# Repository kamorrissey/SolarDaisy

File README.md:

# SolarDaisy

## Introduction
The SolarDaisy is an open-source solar garden light with animated LEDs.
The LEDs animate only in relative darkness.
All files needed to reproduce the device are included.

A 2V solar panel charges an AA 1.2V NiMH cell through a 1N5817 Schottky diode to limit current backflow from the cell to the panel.
The cell (possibly in addition to the panel) is boosted to 3.3V with a TPS613222 boost-buck regulator.
The regulator powers a PIC16F13115 microcontroller (MCU), which drives the LEDs of the light.

There are two groups of LEDs:
* a center color-cycling standard LED is on only when the MCU detects darkness
* a ring of six white, high-brightness, 3V standard LEDs
  are animated using three-wire [Charlieplexing](https://en.wikipedia.org/wiki/Charlieplexing),
  time-division multiplexing, and PWM (for brightness control)

There is a circular main PCB.
A breakaway portion is used in the charging section of the device.

The post and charging section, with a solar panel and battery holder, from a commercial solar garden walkway light are used to simplify manufacturing.
The 3d-printed parts are of modular design so that only one part need be redesigned to use a different walkway light.

## Project Layout
There are four primary folders:
  1. [artifacts](artifacts) - files from the original project deemed worth archiving
  1. [kicad](kicad) - KiCad projects for PCB designs
  1. [mplab](mplab) - MPLAB X projects for the firmware
  1. [solidworks](solidworks) - SOLIDWORKS CAD projects for 3d printable parts

## Building
Can be built with [MPLAB X IDE](https://www.microchip.com/mplab-x-ide)
or [MPLAB for VS Code](https://www.microchip.com/en-us/tools-resources/develop/mplab-tools-vs-code)
by opening the folder mplab/solar-charlie-16f13115.X in the desired MPLAB tool.

(Remainder to be provided)

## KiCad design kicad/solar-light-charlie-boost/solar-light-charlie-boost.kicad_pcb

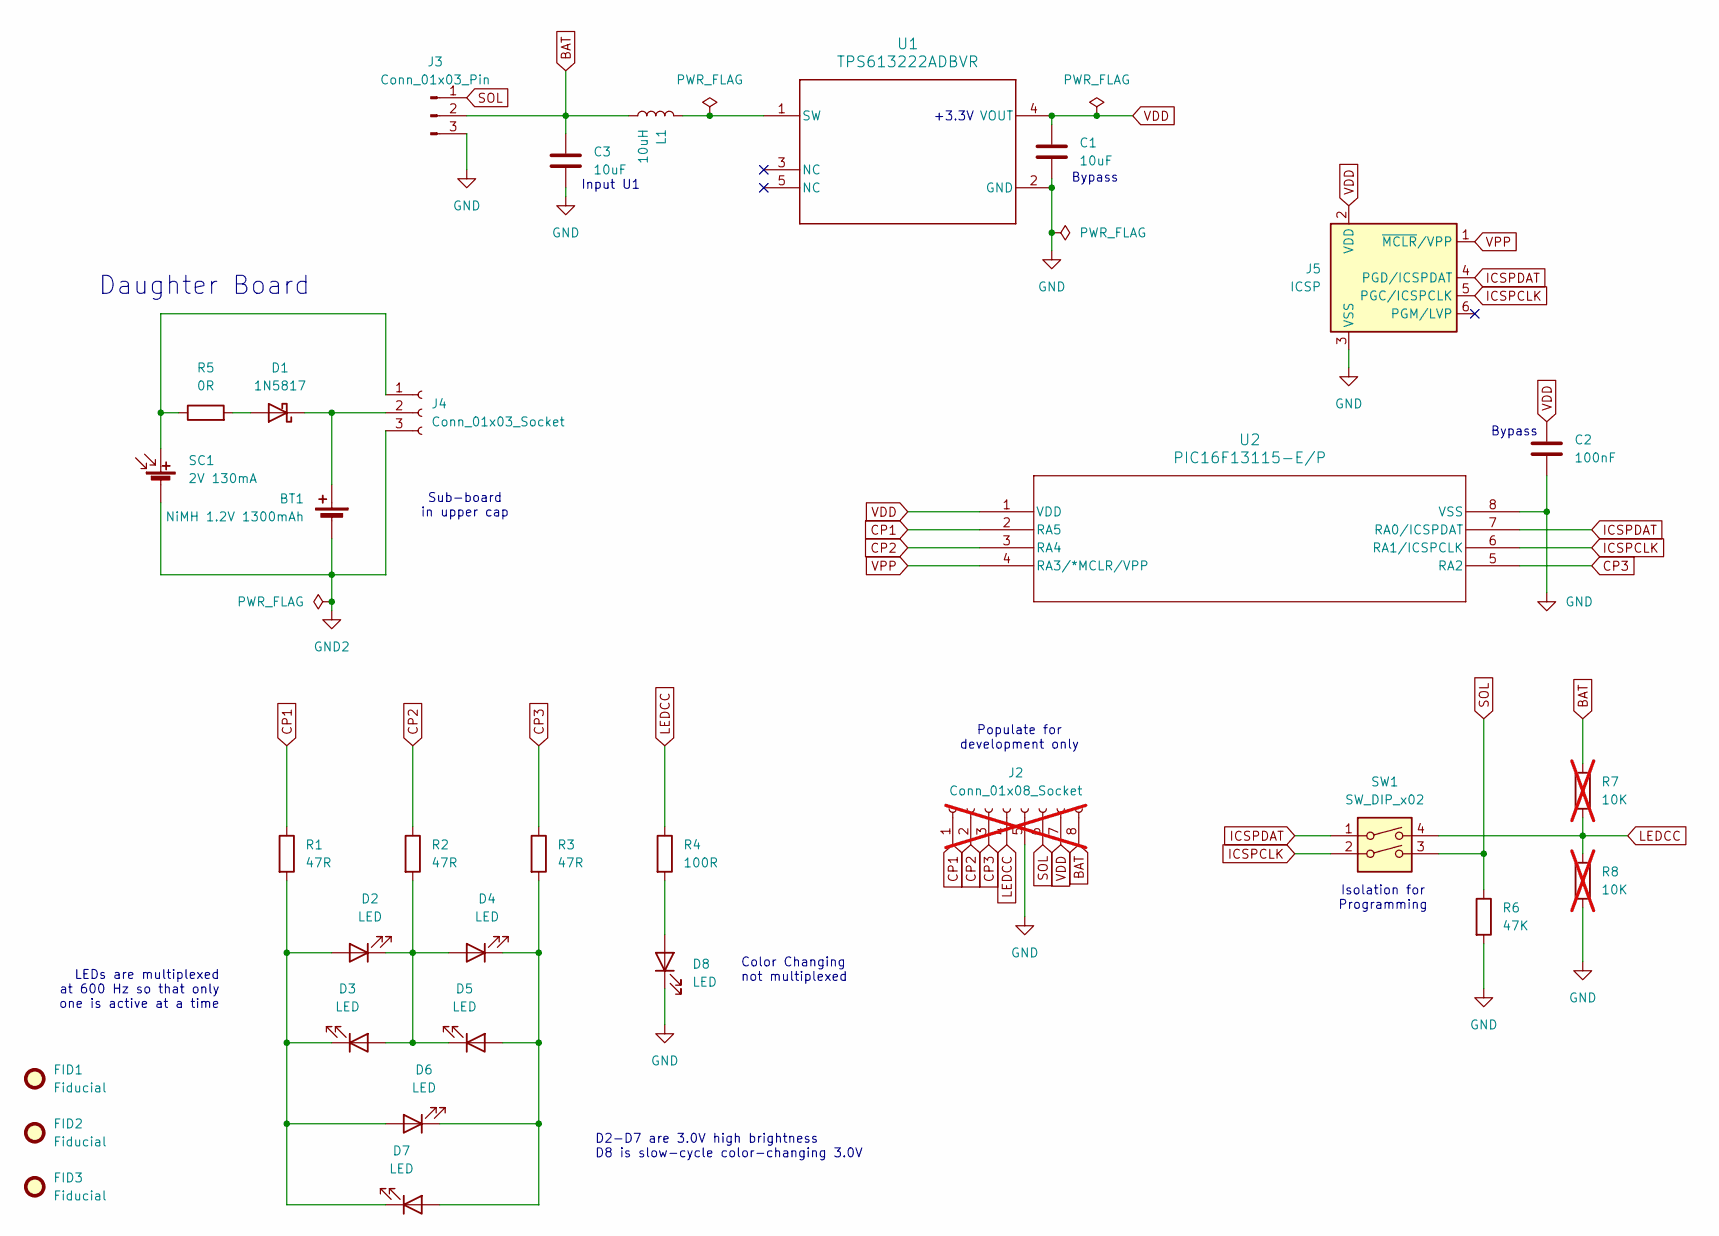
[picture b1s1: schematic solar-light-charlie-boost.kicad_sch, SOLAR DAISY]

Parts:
BT1: NiMH 1.2V 1300mAh; SolderWire-0.1sqmm_1x02_P3.6mm_D0.4mm_OD1mm
C1, C3: 10uF; C_Disc_D3.0mm_W2.0mm_P2.50mm
C2: 100nF; C_Disc_D3.0mm_W2.0mm_P2.50mm
D1: 1N5817; D_DO-41_SOD81_P10.16mm_Horizontal
D2, D3, D4, D5, D6, D7, D8: LED; LED_D5.0mm
FID1, FID2, FID3: Fiducial; Fiducial_0.5mm_Mask1mm
J2: Conn_01x08_Socket; PinSocket_1x08_P2.54mm_Vertical; not fitted
J3: Conn_01x03_Pin; JST_PH_B3B-PH-K_1x03_P2.00mm_Vertical
J4: Conn_01x03_Socket; SolderWire-0.1sqmm_1x03_P3.6mm_D0.4mm_OD1mm
J5: ICSP; PinHeader_1x06_P2.54mm_Horizontal
L1: 10uH; L_Axial_L5.0mm_D3.6mm_P10.00mm_Horizontal_Murata_BL01RN1A2A2
R1, R2, R3: 47R; R_Axial_DIN0207_L6.3mm_D2.5mm_P10.16mm_Horizontal
R4: 100R; R_Axial_DIN0207_L6.3mm_D2.5mm_P10.16mm_Horizontal
R5: 0R; R_Axial_DIN0207_L6.3mm_D2.5mm_P10.16mm_Horizontal
R6: 47K; R_Axial_DIN0207_L6.3mm_D2.5mm_P10.16mm_Horizontal
R7, R8: 10K; R_Axial_DIN0207_L6.3mm_D2.5mm_P10.16mm_Horizontal; not fitted
SC1: 2V 130mA; SolderWire-0.1sqmm_1x02_P3.6mm_D0.4mm_OD1mm
SW1: SW_DIP_x02; SW_DIP_SPSTx02_Slide_6.7x6.64mm_W7.62mm_P2.54mm_LowProfile
U1: TPS613222ADBVR; SOT-23-5_HandSoldering
U2: PIC16F13115-E/P; DIP-8_W7.62mm

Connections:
BAT: C3.1, J2.8, J3.2, L1.1, R7.1
CP1: J2.1, R1.1, U2.2 (RA5)
CP2: J2.2, R2.1, U2.3 (RA4)
CP3: J2.3, R3.1, U2.5 (RA2)
GND: C1.2, C2.1, C3.2, D8.1 (K), J2.5, J3.3, J5.3 (VSS), R6.2, R8.2, U1.2 (GND), U2.8 (VSS)
GND2: BT1.2 (-), J4.3, SC1.2 (-)
ICSPCLK: J5.5 (PGC/ICSPCLK), SW1.2, U2.6 (RA1/ICSPCLK)
ICSPDAT: J5.4 (PGD/ICSPDAT), SW1.1, U2.7 (RA0/ICSPDAT)
LEDCC: J2.4, R4.1, R7.2, R8.1, SW1.4
unnamed: BT1.1 (+), D1.1 (K), J4.2
unnamed: D1.2 (A), R5.2
unnamed: D2.2 (A), D3.1 (K), D6.2 (A), D7.1 (K), R1.2
unnamed: D2.1 (K), D3.2 (A), D4.2 (A), D5.1 (K), R2.2
unnamed: D4.1 (K), D5.2 (A), D6.1 (K), D7.2 (A), R3.2
unnamed: D8.2 (A), R4.2
unnamed: J4.1, R5.1, SC1.1 (+)
unnamed: L1.2, U1.1 (SW)
SOL: J2.6, J3.1, R6.1, SW1.3
VDD: C1.1, C2.2, J2.7, J5.2 (VDD), U1.4 (VOUT), U2.1 (VDD)
VPP: J5.1 (~MCLR/VPP), U2.4 (RA3/*MCLR/VPP)

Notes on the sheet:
Isolation for Programming
LEDs are multiplexed at 600 Hz so that only one is active at a time
+3.3V
Input U1
Daughter Board
Sub-board in upper cap
Bypass
D2-D7 are 3.0V high brightness D8 is slow-cycle color-changing 3.0V
Color Changing not multiplexed
Populate for development only

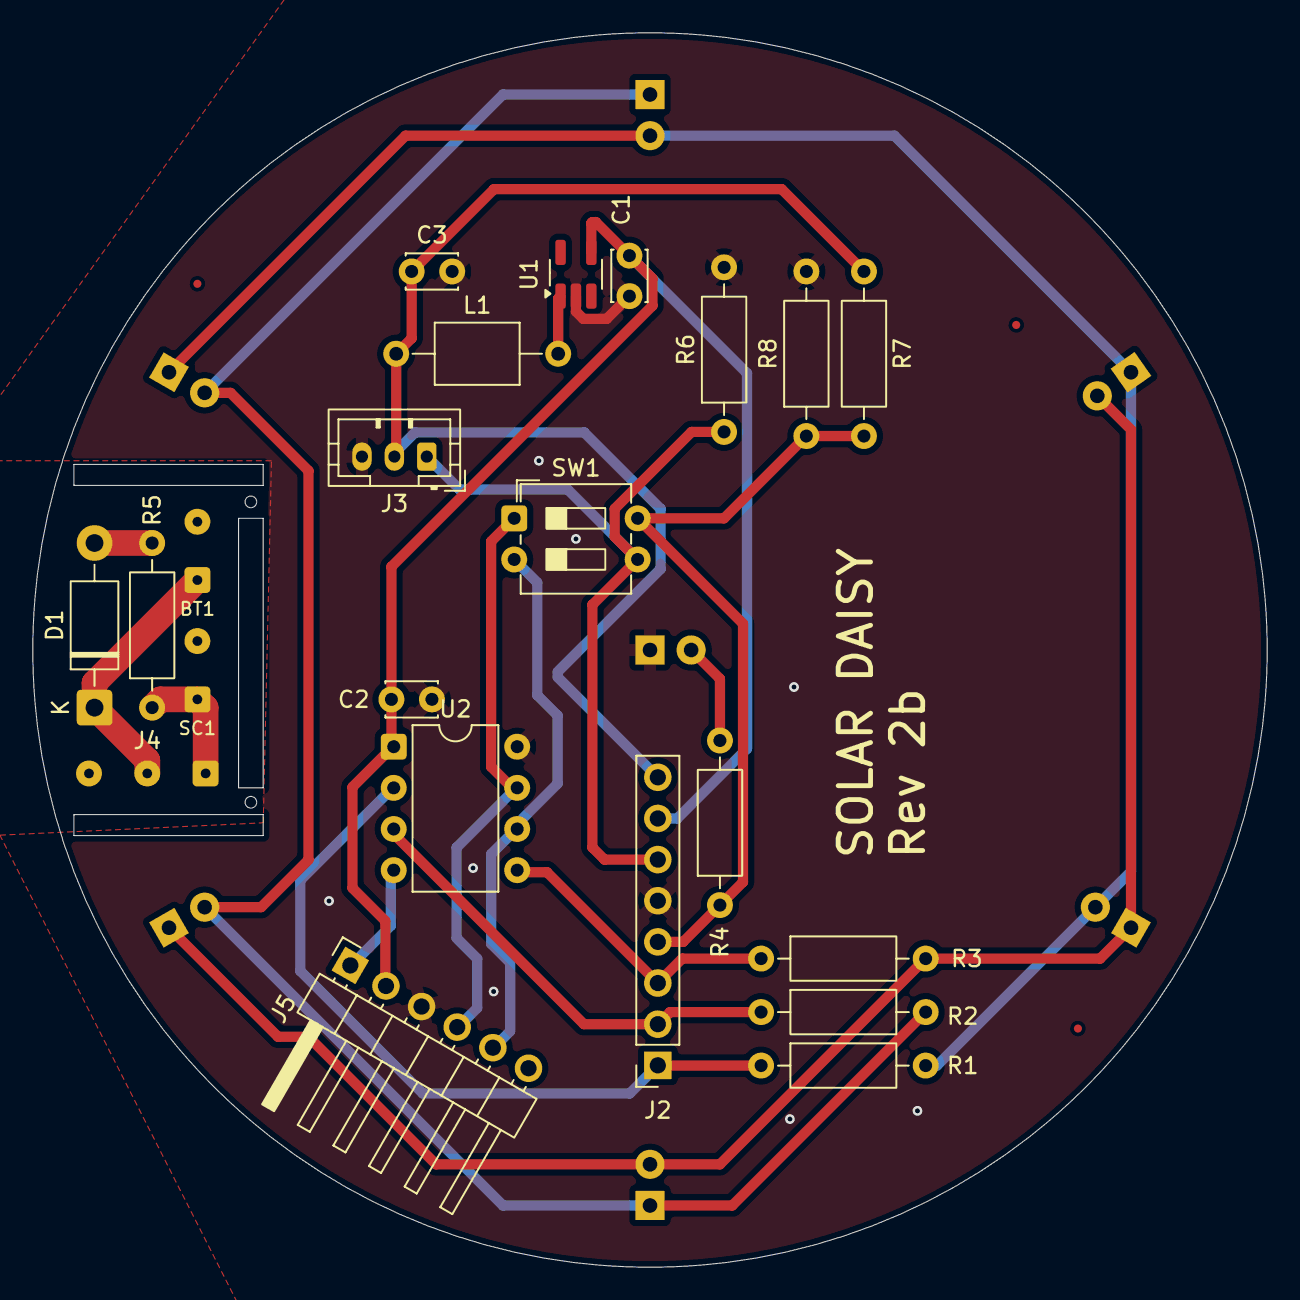
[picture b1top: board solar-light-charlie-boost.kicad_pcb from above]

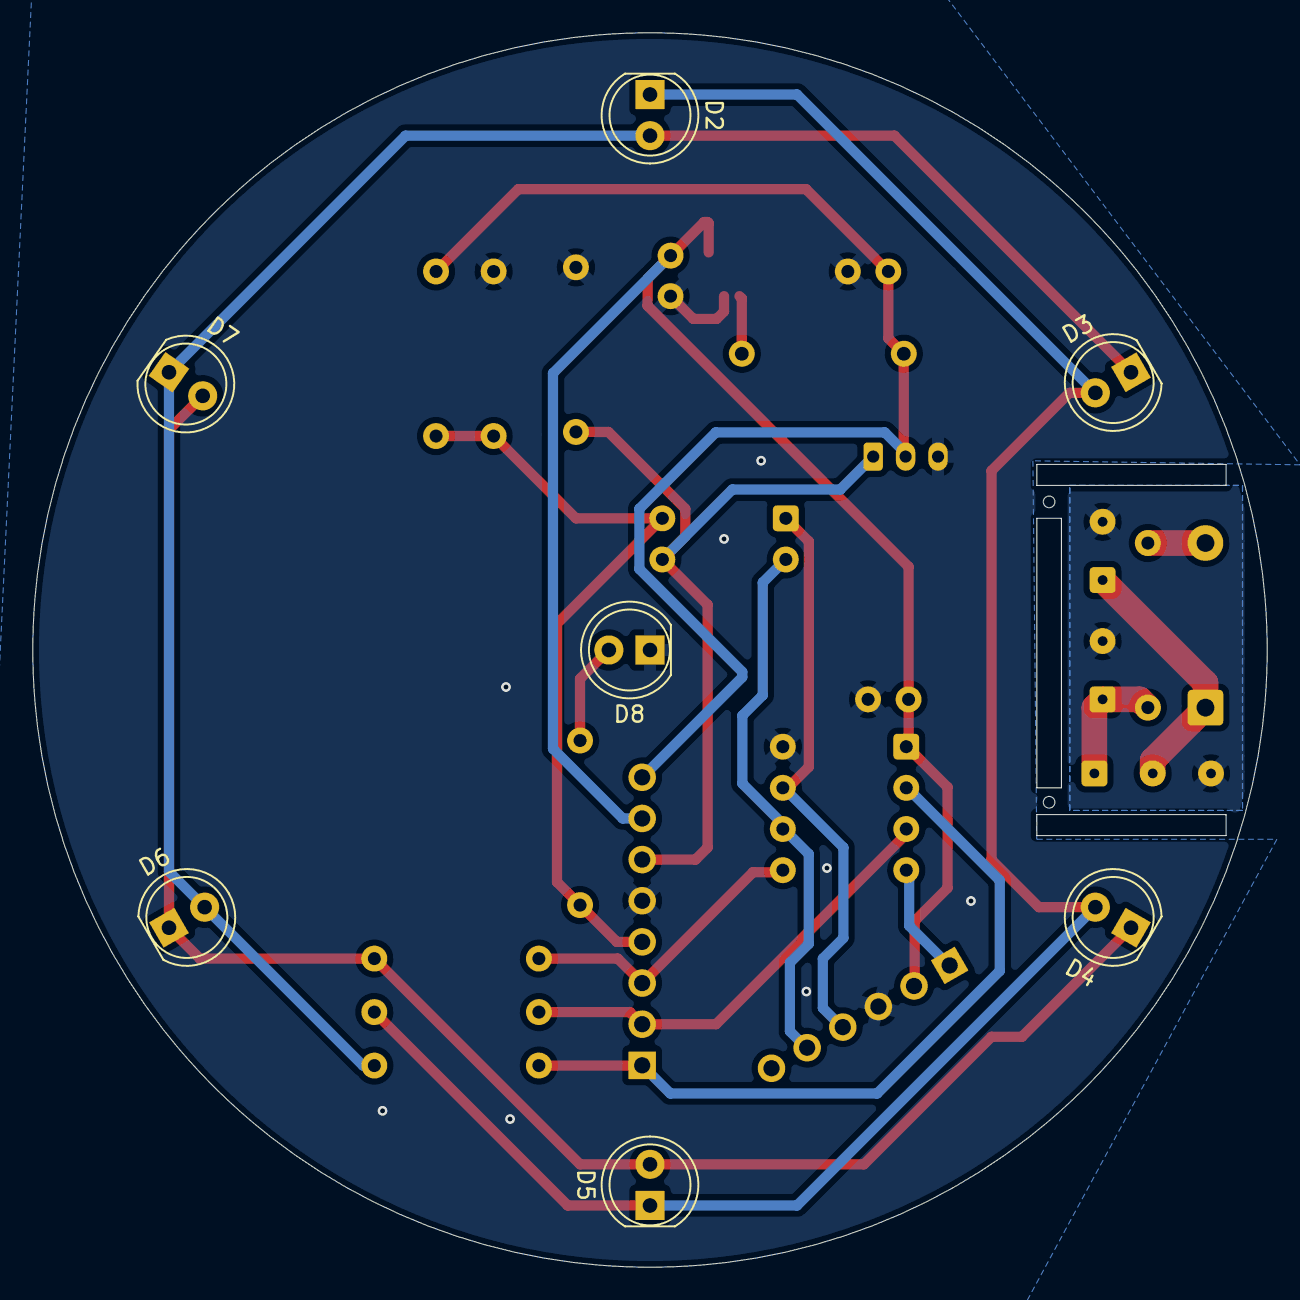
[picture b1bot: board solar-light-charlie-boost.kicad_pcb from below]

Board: 2 copper layers, 76.2 x 76.2 mm, 32 parts (7 on the bottom side), 20 nets.

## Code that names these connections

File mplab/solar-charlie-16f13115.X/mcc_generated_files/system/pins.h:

/**
 * Generated Pins header File
 * 
 * @file pins.h
 * 
 * @defgroup  pinsdriver Pins Driver
 * 
 * @brief This is generated driver header for pins. 
 *        This header file provides APIs for all pins selected in the GUI.
 *
 * @version Driver Version  3.0.0
*/

/*
© [2026] Microchip Technology Inc. and its subsidiaries.

    Subject to your compliance with these terms, you may use Microchip 
    software and any derivatives exclusively with Microchip products. 
    You are responsible for complying with 3rd party license terms  
    applicable to your use of 3rd party software (including open source  
    software) that may accompany Microchip software. SOFTWARE IS ?AS IS.? 
    NO WARRANTIES, WHETHER EXPRESS, IMPLIED OR STATUTORY, APPLY TO THIS 
    SOFTWARE, INCLUDING ANY IMPLIED WARRANTIES OF NON-INFRINGEMENT,  
    MERCHANTABILITY, OR FITNESS FOR A PARTICULAR PURPOSE. IN NO EVENT 
    WILL MICROCHIP BE LIABLE FOR ANY INDIRECT, SPECIAL, PUNITIVE, 
    INCIDENTAL OR CONSEQUENTIAL LOSS, DAMAGE, COST OR EXPENSE OF ANY 
    KIND WHATSOEVER RELATED TO THE SOFTWARE, HOWEVER CAUSED, EVEN IF 
    MICROCHIP HAS BEEN ADVISED OF THE POSSIBILITY OR THE DAMAGES ARE 
    FORESEEABLE. TO THE FULLEST EXTENT ALLOWED BY LAW, MICROCHIP?S 
    TOTAL LIABILITY ON ALL CLAIMS RELATED TO THE SOFTWARE WILL NOT 
    EXCEED AMOUNT OF FEES, IF ANY, YOU PAID DIRECTLY TO MICROCHIP FOR 
    THIS SOFTWARE.
*/

#ifndef PINS_H
#define PINS_H

#include <xc.h>

#define INPUT   1
#define OUTPUT  0

#define HIGH    1
#define LOW     0

#define ANALOG      1
#define DIGITAL     0

#define PULL_UP_ENABLED      1
#define PULL_UP_DISABLED     0

// get/set IO_RA0 aliases
#define LEDCC_TRIS                 TRISAbits.TRISA0
#define LEDCC_LAT                  LATAbits.LATA0
#define LEDCC_PORT                 PORTAbits.RA0
#define LEDCC_WPU                  WPUAbits.WPUA0
#define LEDCC_OD                   ODCONAbits.ODCA0
#define LEDCC_ANS                  ANSELAbits.ANSA0
#define LEDCC_SetHigh()            do { LATAbits.LATA0 = 1; } while(0)
#define LEDCC_SetLow()             do { LATAbits.LATA0 = 0; } while(0)
#define LEDCC_Toggle()             do { LATAbits.LATA0 = ~LATAbits.LATA0; } while(0)
#define LEDCC_GetValue()           PORTAbits.RA0
#define LEDCC_SetDigitalInput()    do { TRISAbits.TRISA0 = 1; } while(0)
#define LEDCC_SetDigitalOutput()   do { TRISAbits.TRISA0 = 0; } while(0)
#define LEDCC_SetPullup()          do { WPUAbits.WPUA0 = 1; } while(0)
#define LEDCC_ResetPullup()        do { WPUAbits.WPUA0 = 0; } while(0)
#define LEDCC_SetPushPull()        do { ODCONAbits.ODCA0 = 0; } while(0)
#define LEDCC_SetOpenDrain()       do { ODCONAbits.ODCA0 = 1; } while(0)
#define LEDCC_SetAnalogMode()      do { ANSELAbits.ANSA0 = 1; } while(0)
#define LEDCC_SetDigitalMode()     do { ANSELAbits.ANSA0 = 0; } while(0)
// get/set IO_RA1 aliases
#define SOL_TRIS                 TRISAbits.TRISA1
#define SOL_LAT                  LATAbits.LATA1
#define SOL_PORT                 PORTAbits.RA1
#define SOL_WPU                  WPUAbits.WPUA1
#define SOL_OD                   ODCONAbits.ODCA1
#define SOL_ANS                  ANSELAbits.ANSA1
#define SOL_SetHigh()            do { LATAbits.LATA1 = 1; } while(0)
#define SOL_SetLow()             do { LATAbits.LATA1 = 0; } while(0)
#define SOL_Toggle()             do { LATAbits.LATA1 = ~LATAbits.LATA1; } while(0)
#define SOL_GetValue()           PORTAbits.RA1
#define SOL_SetDigitalInput()    do { TRISAbits.TRISA1 = 1; } while(0)
#define SOL_SetDigitalOutput()   do { TRISAbits.TRISA1 = 0; } while(0)
#define SOL_SetPullup()          do { WPUAbits.WPUA1 = 1; } while(0)
#define SOL_ResetPullup()        do { WPUAbits.WPUA1 = 0; } while(0)
#define SOL_SetPushPull()        do { ODCONAbits.ODCA1 = 0; } while(0)
#define SOL_SetOpenDrain()       do { ODCONAbits.ODCA1 = 1; } while(0)
#define SOL_SetAnalogMode()      do { ANSELAbits.ANSA1 = 1; } while(0)
#define SOL_SetDigitalMode()     do { ANSELAbits.ANSA1 = 0; } while(0)
// get/set IO_RA2 aliases
#define CP3_TRIS                 TRISAbits.TRISA2
#define CP3_LAT                  LATAbits.LATA2
#define CP3_PORT                 PORTAbits.RA2
#define CP3_WPU                  WPUAbits.WPUA2
#define CP3_OD                   ODCONAbits.ODCA2
#define CP3_ANS                  ANSELAbits.ANSA2
#define CP3_SetHigh()            do { LATAbits.LATA2 = 1; } while(0)
#define CP3_SetLow()             do { LATAbits.LATA2 = 0; } while(0)
#define CP3_Toggle()             do { LATAbits.LATA2 = ~LATAbits.LATA2; } while(0)
#define CP3_GetValue()           PORTAbits.RA2
#define CP3_SetDigitalInput()    do { TRISAbits.TRISA2 = 1; } while(0)
#define CP3_SetDigitalOutput()   do { TRISAbits.TRISA2 = 0; } while(0)
#define CP3_SetPullup()          do { WPUAbits.WPUA2 = 1; } while(0)
#define CP3_ResetPullup()        do { WPUAbits.WPUA2 = 0; } while(0)
#define CP3_SetPushPull()        do { ODCONAbits.ODCA2 = 0; } while(0)
#define CP3_SetOpenDrain()       do { ODCONAbits.ODCA2 = 1; } while(0)
#define CP3_SetAnalogMode()      do { ANSELAbits.ANSA2 = 1; } while(0)
#define CP3_SetDigitalMode()     do { ANSELAbits.ANSA2 = 0; } while(0)
// get/set IO_RA4 aliases
#define CP2_TRIS                 TRISAbits.TRISA4
#define CP2_LAT                  LATAbits.LATA4
#define CP2_PORT                 PORTAbits.RA4
#define CP2_WPU                  WPUAbits.WPUA4
#define CP2_OD                   ODCONAbits.ODCA4
#define CP2_ANS                  ANSELAbits.ANSA4
#define CP2_SetHigh()            do { LATAbits.LATA4 = 1; } while(0)
#define CP2_SetLow()             do { LATAbits.LATA4 = 0; } while(0)
#define CP2_Toggle()             do { LATAbits.LATA4 = ~LATAbits.LATA4; } while(0)
#define CP2_GetValue()           PORTAbits.RA4
#define CP2_SetDigitalInput()    do { TRISAbits.TRISA4 = 1; } while(0)
#define CP2_SetDigitalOutput()   do { TRISAbits.TRISA4 = 0; } while(0)
#define CP2_SetPullup()          do { WPUAbits.WPUA4 = 1; } while(0)
#define CP2_ResetPullup()        do { WPUAbits.WPUA4 = 0; } while(0)
#define CP2_SetPushPull()        do { ODCONAbits.ODCA4 = 0; } while(0)
#define CP2_SetOpenDrain()       do { ODCONAbits.ODCA4 = 1; } while(0)
#define CP2_SetAnalogMode()      do { ANSELAbits.ANSA4 = 1; } while(0)
#define CP2_SetDigitalMode()     do { ANSELAbits.ANSA4 = 0; } while(0)
// get/set IO_RA5 aliases
#define CP1_TRIS                 TRISAbits.TRISA5
#define CP1_LAT                  LATAbits.LATA5
#define CP1_PORT                 PORTAbits.RA5
#define CP1_WPU                  WPUAbits.WPUA5
#define CP1_OD                   ODCONAbits.ODCA5
#define CP1_ANS                  ANSELAbits.ANSA5
#define CP1_SetHigh()            do { LATAbits.LATA5 = 1; } while(0)
#define CP1_SetLow()             do { LATAbits.LATA5 = 0; } while(0)
#define CP1_Toggle()             do { LATAbits.LATA5 = ~LATAbits.LATA5; } while(0)
#define CP1_GetValue()           PORTAbits.RA5
#define CP1_SetDigitalInput()    do { TRISAbits.TRISA5 = 1; } while(0)
#define CP1_SetDigitalOutput()   do { TRISAbits.TRISA5 = 0; } while(0)
#define CP1_SetPullup()          do { WPUAbits.WPUA5 = 1; } while(0)
#define CP1_ResetPullup()        do { WPUAbits.WPUA5 = 0; } while(0)
#define CP1_SetPushPull()        do { ODCONAbits.ODCA5 = 0; } while(0)
#define CP1_SetOpenDrain()       do { ODCONAbits.ODCA5 = 1; } while(0)
#define CP1_SetAnalogMode()      do { ANSELAbits.ANSA5 = 1; } while(0)
#define CP1_SetDigitalMode()     do { ANSELAbits.ANSA5 = 0; } while(0)
/**
 * @ingroup  pinsdriver
 * @brief GPIO and peripheral I/O initialization
 * @param none
 * @return none
 */
void PIN_MANAGER_Initialize (void);

/**
 * @ingroup  pinsdriver
 * @brief Interrupt on Change Handling routine
 * @param none
 * @return none
 */
void PIN_MANAGER_IOC(void);


#endif // PINS_H
/**
 End of File
*/
